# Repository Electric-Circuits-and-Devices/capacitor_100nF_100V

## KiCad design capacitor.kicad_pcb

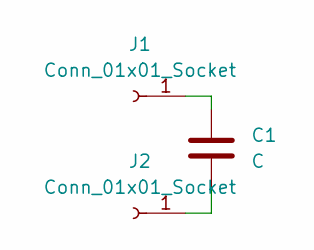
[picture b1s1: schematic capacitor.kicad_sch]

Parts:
C1: C; C_1206_3216Metric
J1, J2: Conn_01x01_Socket; MountingHole_2.5mm_Pad

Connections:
unnamed: C1.1, J1.1
unnamed: C1.2, J2.1

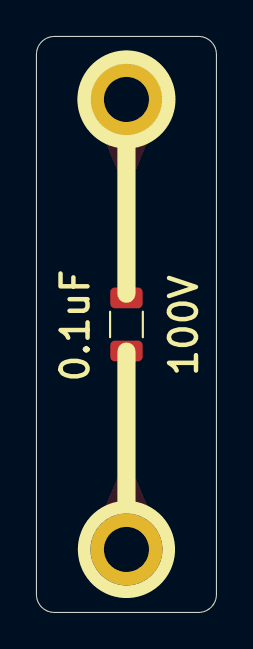
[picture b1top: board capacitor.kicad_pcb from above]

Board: 2 copper layers, 10.0 x 32.0 mm, 3 parts (0 on the bottom side), 2 nets.
